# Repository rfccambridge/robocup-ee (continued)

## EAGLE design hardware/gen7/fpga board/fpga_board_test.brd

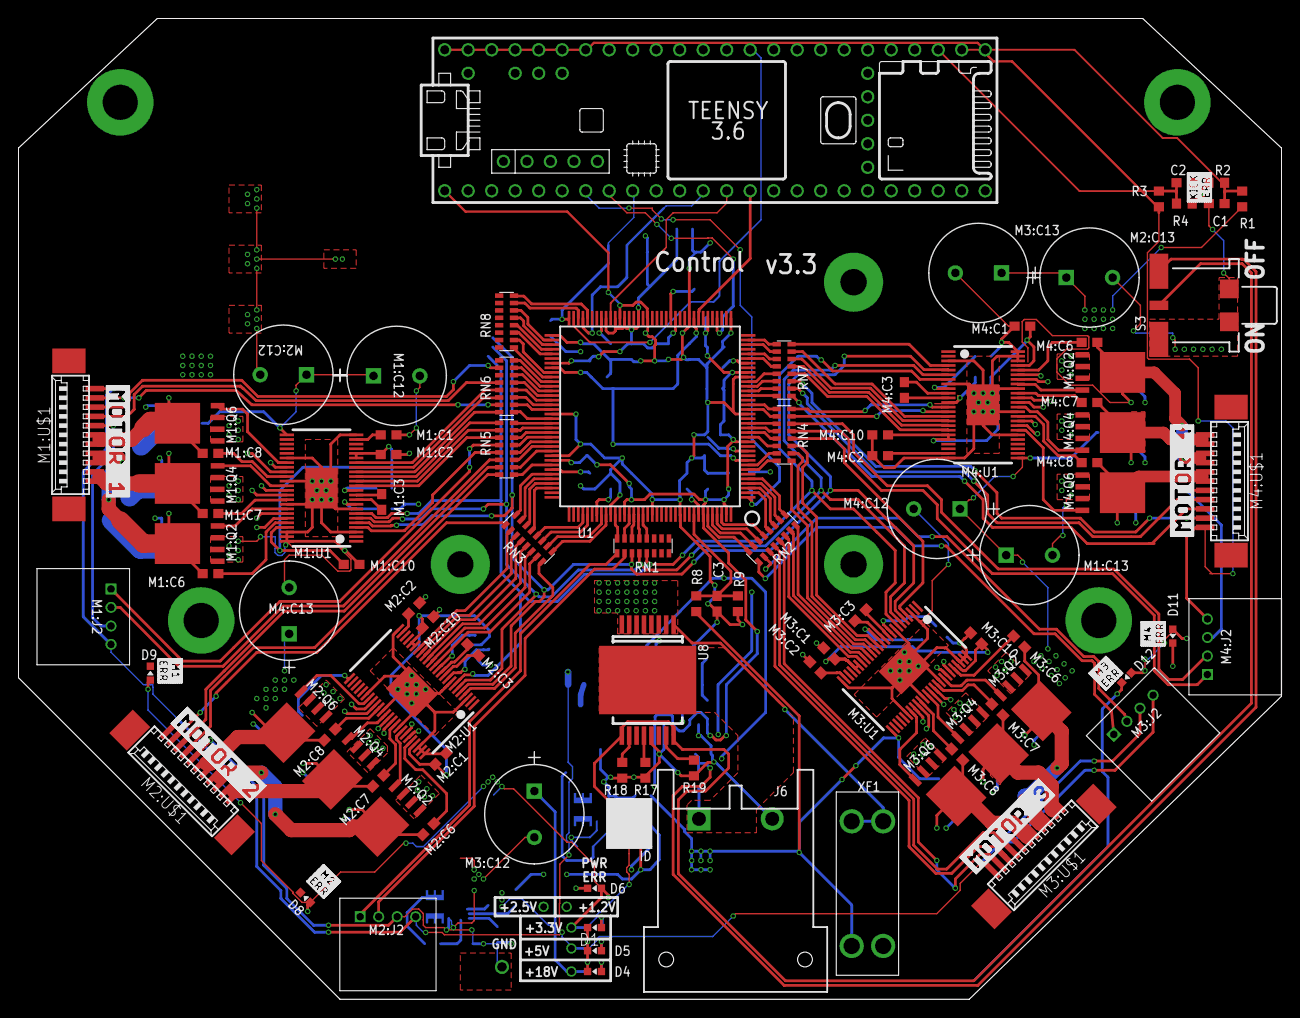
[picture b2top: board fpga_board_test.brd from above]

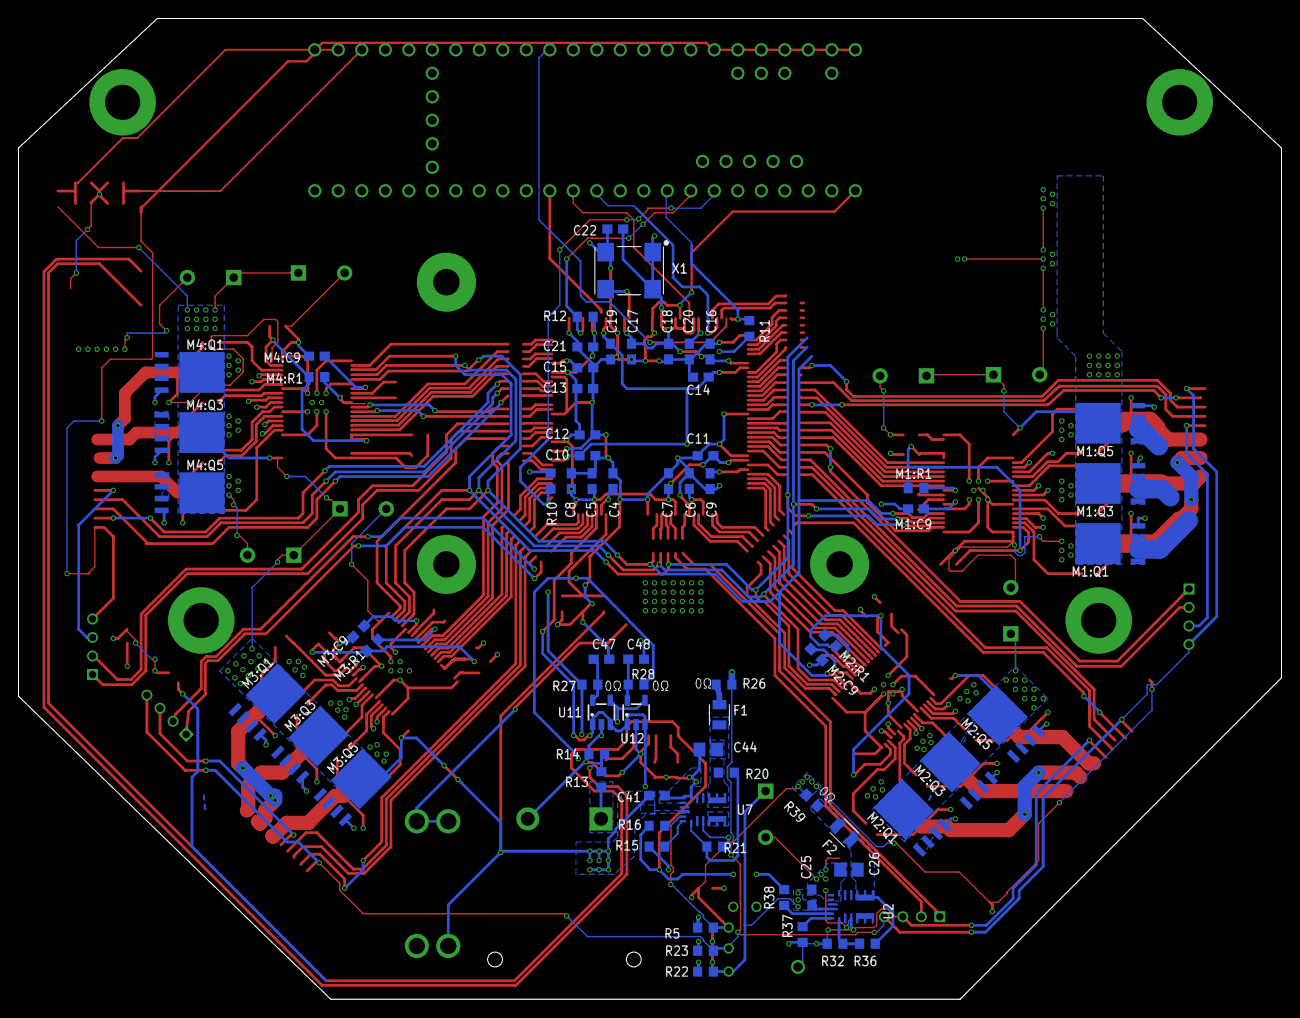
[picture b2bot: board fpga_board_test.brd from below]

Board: 6 copper layers, 136.5 x 106.0 mm, 175 parts (72 on the bottom side), 224 nets.

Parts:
C1: 0.1uF 50V; C0603
C2, C3, C4, C5, C6, C7, C8, C9, C10, C11, C12, C13, C14, C15, C16, C17, C18, C19, C20, C21, C22: 0.1uF; C0603
C25, C41: GRM188R6YA106MA73D; C0603
C26, C44: 22uF 16V; C0805
C47, C48: 1uF; C0603
D1, D4, D5: GREEN; CHIP-LED0603
D6, D8, D9, D11, D12: RED; CHIP-LED0603
F1, F2: 0805L200SLTHYR; FUSC2113X75
J6: DF22-2; DF22-2-H
M1:C1, M1:C2, M2:C1, M2:C2, M3:C1, M3:C2, M4:C1, M4:C2: 1uF; C0603
M1:C3, M2:C3, M3:C3, M4:C3: 0.022uF 50V; C0603
M1:C6, M1:C7, M1:C8, M1:C10, M2:C6, M2:C7, M2:C8, M2:C10, M3:C6, M3:C7, M3:C8, M3:C10, M4:C6, M4:C7, M4:C8, M4:C10: 0.1uF 50V; C0603
M1:C9, M2:C9, M3:C9, M4:C9: 2.2uF 50V; C0603
M1:C12, M1:C13, M2:C12, M2:C13, M3:C12, M3:C13, M4:C12, M4:C13: ECA-1HHG221; CAP_PAN_10X12.5
M1:J2, M2:J2, M3:J2, M4:J2: 4-PIN_2MM-H; 2MM-4-H
M1:Q1, M1:Q2, M1:Q3, M1:Q4, M1:Q5, M1:Q6, M2:Q1, M2:Q2, M2:Q3, M2:Q4, M2:Q5, M2:Q6, M3:Q1, M3:Q2, M3:Q3, M3:Q4, M3:Q5, M3:Q6, M4:Q1, M4:Q2, M4:Q3, M4:Q4, M4:Q5, M4:Q6: IRFH7545; PQFN_5X6_E
M1:R1, M2:R1, M3:R1, M4:R1: 10k; R0603
M1:U1, M2:U1, M3:U1, M4:U1: DRV8303DCA; TSSOP-48_PAD
M1:U$1, M2:U$1, M3:U$1, M4:U$1: MOTORCON; GEN3CON
R1: 68k 1%; R0603
R2, R3, R4: 10k 1%; R0603
R5, R18, R19, R22, R23: 1k; R0603
R8: 68k; R0603
R9, R17: 10k; R0603
R10, R12: 4.7k; R0603
R11: 330; R0603
R13: 270k; R0603
R14: 100k; R0603
R15: 43.2k; R0603
R16, R38: 150k; R0603
R20, R36: 160k 1%; R0603
R21: 30.1k 1%; R0603
R26, R27, R28, R39: 0; R0603
R32: 51.0k 1%; R0603
R37: 29.4k; R0603
RN1, RN2, RN3, RN4, RN5, RN6, RN7, RN8: 330; RA-8_2506
S3: 34EWMSP12M6RT
U1: XC3S250E-4TQG144C; TQFP144
U2, U7: MPM3620GQV-P
U8: VND5E006ASPTR-E; POWERSO-16
U11: MCP1824T-1202E/OT; SOT-23-5
U12: MCP1824T-2502E/OT; SOT-23-5
U$3: MOTOR-1
U$5: MOTOR-2
U$6: MOTOR-3
U$7: MOTOR-4
U$8: ERR-M1
U$10: TEENSY_3.5/3.6
U$12: ERR-M2
U$13: ERR-M3
U$14: ERR-M4
U$15: ERR-KICK
X1: ASV-18.432MHZ-EJ-T; ASV
XF1: 30A; 3557-2

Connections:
5V-LED: D5.A, R23.2
5V-LED1: D1.A, R5.2
18.5V-LED: D4.A, R22.1
!CS!-FPGA: U1.69, U$10.10/CS
+1.2V: C6.1, C10.1, C14.1, C19.1, R27.2, U1.9, U1.45, U1.80, U1.115
+1.2V-PRE: C47.1, R27.1, U11.5
+2.5V: C4.1, C9.1, C15.1, C20.1, R10.2, R11.2, R28.2, U1.30, U1.65, U1.102, U1.137
+2.5V-PRE: C48.1, R28.1, U12.5
+3.3V: C5.1, C7.1, C8.1, C11.1, C12.1, C13.1, C16.1, C17.1, C18.1, C21.1, C22.1, D6.A, D8.A, D9.A, D11.A, D12.A, R5.1, R12.1, R39.2, U1.13, U1.28, U1.42, U1.49, U1.57, U1.60, U1.62, U1.64, U1.79, U1.100, U1.121, U1.138, U1.143, U11.1, U11.3, U12.1, U12.3, X1.1, X1.4
+3.3V-FUSE: C26.1, F2.1, R36.2, U2.789
+5V: M1:J2.4, M1:U$1.1, M2:J2.4, M2:U$1.1, M3:J2.4, M3:U$1.1, M4:J2.4, M4:U$1.1, R3.1, R23.1, R26.2, U$10.VIN
+5V-FUSE: C44.1, F1.1, R20.2, U7.789
+18.5V: C25.1, C41.1, M1:C12.1, M1:C13.1, M1:Q1.5678, M1:Q3.5678, M1:Q5.5678, M1:U1.25, M2:C12.1, M2:C13.1, M2:Q1.5678, M2:Q3.5678, M2:Q5.5678, M2:U1.25, M3:C12.1, M3:C13.1, M3:Q1.5678, M3:Q3.5678, M3:Q5.5678, M3:U1.25, M4:C12.1, M4:C13.1, M4:Q1.5678, M4:Q3.5678, M4:Q5.5678, M4:U1.25, R1.1, R8.1, R22.2, U2.16, U7.16, XF1.3, XF1.4
AAM: R15.2, U7.18
AAM1: R37.2, U2.18
BATT-FPGA: C3.1, R8.2, R9.1, U1.136
CS1: R18.2, U8.10
CS2: R19.2, U8.15
CS-DIS: R17.2, U8.12
EN: R16.2, U7.17
EN1: R38.2, U2.17
EN-PWR: R16.1, R38.1, S3.2, U8.9, U8.16
EN-PWR-PRE: R13.1, R14.2, S3.1
FB: R20.1, R21.2, U7.1
FB1: R32.2, R36.1, U2.1
FPGA-CLK: U1.50, X1.3
FPGA-DONE: R11.1, U1.72, U$10.7
FPGA-INIT: R12.2, U1.40, U$10.6
FPGA-PROG: R10.1, U1.1, U$10.5
GND: C1.2, C2.2, C3.2, C4.2, C5.2, C6.2, C7.2, C8.2, C9.2, C10.2, C11.2, C12.2, C13.2, C14.2, C15.2, C16.2, C17.2, C18.2, C19.2, C20.2, C21.2, C22.2, C25.2, C26.2, C41.2, C44.2, C47.2, C48.2, D1.C, D4.C, D5.C, J6.2, M1:C1.2, M1:C2.2, M1:C9.2, M1:C10.2, M1:C12.2, M1:C13.2, M1:J2.3, M1:Q2.1, M1:Q2.2, M1:Q2.3, M1:Q4.1, M1:Q4.2, M1:Q4.3, M1:Q6.1, M1:Q6.2, M1:Q6.3, M1:U1.3, M1:U1.8, M1:U1.24, M1:U1.30, M1:U1.35, M1:U1.40, M1:U1.46, M1:U1.47, M1:U1.48, M1:U1.PAD, M1:U$1.5, M2:C1.2, M2:C2.2, M2:C9.2, M2:C10.2, M2:C12.2, M2:C13.2, M2:J2.3, M2:Q2.1, M2:Q2.2, M2:Q2.3, M2:Q4.1, M2:Q4.2, M2:Q4.3, M2:Q6.1, M2:Q6.2, M2:Q6.3, M2:U1.3, M2:U1.8, M2:U1.24, M2:U1.30, M2:U1.35, M2:U1.40, M2:U1.46, M2:U1.47, M2:U1.48, M2:U1.PAD, M2:U$1.5, M3:C1.2, M3:C2.2, M3:C9.2, M3:C10.2, M3:C12.2, M3:C13.2, M3:J2.3, M3:Q2.1, M3:Q2.2, M3:Q2.3, M3:Q4.1, M3:Q4.2, M3:Q4.3, M3:Q6.1, M3:Q6.2, M3:Q6.3, M3:U1.3, M3:U1.8, M3:U1.24, M3:U1.30, M3:U1.35, M3:U1.40, M3:U1.46, M3:U1.47, M3:U1.48, M3:U1.PAD, M3:U$1.5, M4:C1.2, M4:C2.2, M4:C9.2, M4:C10.2, M4:C12.2, M4:C13.2, M4:J2.3, M4:Q2.1, M4:Q2.2, M4:Q2.3, M4:Q4.1, M4:Q4.2, M4:Q4.3, M4:Q6.1, M4:Q6.2, M4:Q6.3, M4:U1.3, M4:U1.8, M4:U1.24, M4:U1.30, M4:U1.35, M4:U1.40, M4:U1.46, M4:U1.47, M4:U1.48, M4:U1.PAD, M4:U$1.5, R2.2, R4.2, R9.2, R14.1, R15.1, R17.1, R18.1, R19.1, R21.1, R32.1, R37.1, S3.3, S3.LEG1, S3.LEG3, U1.11, U1.19, U1.27, U1.37, U1.46, U1.55, U1.61, U1.73, U1.90, U1.99, U1.118, U1.127, U1.133, U2.3, U2.12, U2.13, U2.14, U7.3, U7.12, U7.13, U7.14, U8.13, U11.2, U12.2, U$10.GND, X1.2
M1-!CS: M1:U1.4, RN5.13
M1-A-H: M1:U1.15, RN5.9
M1-A-L: M1:U1.16, RN6.16
M1-B-H: M1:U1.13, RN5.11
M1-B-L: M1:U1.14, RN5.10
M1-C-H: M1:U1.17, RN6.14
M1-C-L: M1:U1.18, RN6.13
M1-ENC-A: M1:J2.2, RN5.14
M1-ENC-B: M1:J2.1, RN5.12
M1-H1: M1:U$1.3, RN6.10
M1-H2: M1:U$1.4, RN6.12
M1-H3: M1:U$1.2, RN6.15
M1:+3.3V: M1:C1.1, M1:C10.1, M1:R1.1, M1:U1.19, M1:U1.20, M1:U1.45
M1:AVDD: M1:C2.1, M1:U1.23
M1:BST-A: M1:C6.1, M1:U1.44
M1:BST-B: M1:C7.1, M1:U1.39
M1:BST-C: M1:C8.1, M1:U1.34
M1:CP1: M1:C3.1, M1:U1.10
M1:CP2: M1:C3.2, M1:U1.11
M1:EN-GATE: M1:R1.2, M1:U1.12
M1:GH-A: M1:Q1.4, M1:U1.43
M1:GH-B: M1:Q3.4, M1:U1.38
M1:GH-C: M1:Q5.4, M1:U1.33
M1:GL-A: M1:Q2.4, M1:U1.41
M1:GL-B: M1:Q4.4, M1:U1.36
M1:GL-C: M1:Q6.4, M1:U1.31
M1:GVDD: M1:C9.1, M1:U1.9
M1:PHASE-A: M1:C7.2, M1:Q3.1, M1:Q3.2, M1:Q3.3, M1:Q4.5678, M1:U1.37, M1:U$1.10, M1:U$1.11
M1:PHASE-B: M1:C6.2, M1:Q1.1, M1:Q1.2, M1:Q1.3, M1:Q2.5678, M1:U1.42, M1:U$1.8, M1:U$1.9
M1:PHASE-C: M1:C8.2, M1:Q5.1, M1:Q5.2, M1:Q5.3, M1:Q6.5678, M1:U1.32, M1:U$1.6, M1:U$1.7
M2-!CS: M2:U1.4, RN3.16
M2-A-H: M2:U1.15, RN3.13
M2-A-L: M2:U1.16, RN3.12
M2-B-H: M2:U1.13, RN3.15
M2-B-L: M2:U1.14, RN3.14
M2-C-H: M2:U1.17, RN3.11
M2-C-L: M2:U1.18, RN3.10
M2-ENC-A: M2:J2.2, RN1.10
M2-ENC-B: M2:J2.1, RN1.9
M2-H1: M2:U$1.3, RN5.15
M2-H2: M2:U$1.4, RN5.16
M2-H3: M2:U$1.2, RN3.9
M2:+3.3V: M2:C1.1, M2:C10.1, M2:R1.1, M2:U1.19, M2:U1.20, M2:U1.45
M2:AVDD: M2:C2.1, M2:U1.23
M2:BST-A: M2:C6.1, M2:U1.44
M2:BST-B: M2:C7.1, M2:U1.39
M2:BST-C: M2:C8.1, M2:U1.34
M2:CP1: M2:C3.1, M2:U1.10
M2:CP2: M2:C3.2, M2:U1.11
M2:EN-GATE: M2:R1.2, M2:U1.12
M2:GH-A: M2:Q1.4, M2:U1.43
M2:GH-B: M2:Q3.4, M2:U1.38
M2:GH-C: M2:Q5.4, M2:U1.33
M2:GL-A: M2:Q2.4, M2:U1.41
M2:GL-B: M2:Q4.4, M2:U1.36
M2:GL-C: M2:Q6.4, M2:U1.31
M2:GVDD: M2:C9.1, M2:U1.9
M2:PHASE-A: M2:C7.2, M2:Q3.1, M2:Q3.2, M2:Q3.3, M2:Q4.5678, M2:U1.37, M2:U$1.10, M2:U$1.11
M2:PHASE-B: M2:C6.2, M2:Q1.1, M2:Q1.2, M2:Q1.3, M2:Q2.5678, M2:U1.42, M2:U$1.8, M2:U$1.9
M2:PHASE-C: M2:C8.2, M2:Q5.1, M2:Q5.2, M2:Q5.3, M2:Q6.5678, M2:U1.32, M2:U$1.6, M2:U$1.7
M3-!CS: M3:U1.4, RN4.12
M3-A-H: M3:U1.15, RN4.9
M3-A-L: M3:U1.16, RN2.16
M3-B-H: M3:U1.13, RN4.11
M3-B-L: M3:U1.14, RN4.10
M3-C-H: M3:U1.17, RN2.15
M3-C-L: M3:U1.18, RN2.14
M3-ENC-A: M3:J2.2, RN2.10
M3-ENC-B: M3:J2.1, RN2.9
M3-H1: M3:U$1.3, RN2.11
M3-H2: M3:U$1.4, RN2.12
M3-H3: M3:U$1.2, RN2.13
M3:+3.3V: M3:C1.1, M3:C10.1, M3:R1.1, M3:U1.19, M3:U1.20, M3:U1.45
M3:AVDD: M3:C2.1, M3:U1.23
M3:BST-A: M3:C6.1, M3:U1.44
M3:BST-B: M3:C7.1, M3:U1.39
M3:BST-C: M3:C8.1, M3:U1.34
M3:CP1: M3:C3.1, M3:U1.10
M3:CP2: M3:C3.2, M3:U1.11
M3:EN-GATE: M3:R1.2, M3:U1.12
M3:GH-A: M3:Q1.4, M3:U1.43
M3:GH-B: M3:Q3.4, M3:U1.38
M3:GH-C: M3:Q5.4, M3:U1.33
M3:GL-A: M3:Q2.4, M3:U1.41
M3:GL-B: M3:Q4.4, M3:U1.36
M3:GL-C: M3:Q6.4, M3:U1.31
M3:GVDD: M3:C9.1, M3:U1.9
M3:PHASE-A: M3:C7.2, M3:Q3.1, M3:Q3.2, M3:Q3.3, M3:Q4.5678, M3:U1.37, M3:U$1.10, M3:U$1.11
M3:PHASE-B: M3:C6.2, M3:Q1.1, M3:Q1.2, M3:Q1.3, M3:Q2.5678, M3:U1.42, M3:U$1.8, M3:U$1.9
M3:PHASE-C: M3:C8.2, M3:Q5.1, M3:Q5.2, M3:Q5.3, M3:Q6.5678, M3:U1.32, M3:U$1.6, M3:U$1.7
M4-!CS: M4:U1.4, RN7.16
M4-A-H: M4:U1.15, RN7.15
M4-A-L: M4:U1.16, RN7.14
M4-B-H: M4:U1.13, RN4.16
M4-B-L: M4:U1.14, RN4.15
M4-C-H: M4:U1.17, RN7.13
M4-C-L: M4:U1.18, RN7.12
M4-ENC-A: M4:J2.2, RN4.14
M4-ENC-B: M4:J2.1, RN4.13
M4-H1: M4:U$1.3, RN7.9
M4-H2: M4:U$1.4, RN7.10
M4-H3: M4:U$1.2, RN7.11
M4:+3.3V: M4:C1.1, M4:C10.1, M4:R1.1, M4:U1.19, M4:U1.20, M4:U1.45
M4:AVDD: M4:C2.1, M4:U1.23
M4:BST-A: M4:C6.1, M4:U1.44
M4:BST-B: M4:C7.1, M4:U1.39
M4:BST-C: M4:C8.1, M4:U1.34
M4:CP1: M4:C3.1, M4:U1.10
M4:CP2: M4:C3.2, M4:U1.11
M4:EN-GATE: M4:R1.2, M4:U1.12
M4:GH-A: M4:Q1.4, M4:U1.43
M4:GH-B: M4:Q3.4, M4:U1.38
M4:GH-C: M4:Q5.4, M4:U1.33
M4:GL-A: M4:Q2.4, M4:U1.41
M4:GL-B: M4:Q4.4, M4:U1.36
M4:GL-C: M4:Q6.4, M4:U1.31
M4:GVDD: M4:C9.1, M4:U1.9
M4:PHASE-A: M4:C7.2, M4:Q3.1, M4:Q3.2, M4:Q3.3, M4:Q4.5678, M4:U1.37, M4:U$1.10, M4:U$1.11
M4:PHASE-B: M4:C6.2, M4:Q1.1, M4:Q1.2, M4:Q1.3, M4:Q2.5678, M4:U1.42, M4:U$1.8, M4:U$1.9
M4:PHASE-C: M4:C8.2, M4:Q5.1, M4:Q5.2, M4:Q5.3, M4:Q6.5678, M4:U1.32, M4:U$1.6, M4:U$1.7
MISO-AUX: M1:U1.6, M2:U1.6, M3:U1.6, M4:U1.6, RN1.12
MISO-FPGA: U1.44, U$10.12/MISO
MOSI-AUX: M1:U1.5, M2:U1.5, M3:U1.5, M4:U1.5, RN1.11
MOSI-FPGA: U1.63, U$10.11/MOSI
unnamed: F2.2, R39.1
unnamed: F1.2, R26.1
PWR-ERR: D6.C, U11.4, U12.4
R-P1: RN8.1, U1.82
R-P2: RN8.2, U1.81
R-P3: RN8.3, U1.77
R-P4: RN8.4, U1.76
R-P5: RN8.5, U1.75
R-P6: RN8.6, U1.74
R-P7: RN8.7, U1.70
R-P8: RN8.8, U1.68
R-P9: RN6.1, U1.91
R-P10: RN6.2, U1.89
R-P11: RN6.3, U1.88
R-P12: RN6.4, U1.87
R-P13: RN6.5, U1.86
R-P14: RN6.6, U1.85
R-P15: RN6.7, U1.84
R-P16: RN6.8, U1.83
R-P17: RN5.1, U1.101
R-P18: RN5.2, U1.98
R-P19: RN5.3, U1.97
R-P20: RN5.4, U1.96
R-P21: RN5.5, U1.95
R-P22: RN5.6, U1.94
R-P23: RN5.7, U1.93
R-P24: RN5.8, U1.92
R-P25: RN3.1, U1.117
R-P26: RN3.2, U1.116
R-P27: RN3.3, U1.113
R-P28: RN3.4, U1.112
R-P29: RN3.5, U1.106
R-P30: RN3.6, U1.105
R-P31: RN3.7, U1.104
R-P32: RN3.8, U1.103
R-P36: RN1.4, U1.125
R-P37: RN1.5, U1.124
R-P38: RN1.6, U1.123
R-P39: RN1.7, U1.122
R-P40: RN1.8, U1.119
R-P41: RN2.1, U1.5
R-P42: RN2.2, U1.4
R-P43: RN2.3, U1.3
R-P44: RN2.4, U1.2
R-P45: RN2.5, U1.142
R-P46: RN2.6, U1.141
R-P47: RN2.7, U1.140
R-P48: RN2.8, U1.139
R-P49: RN4.1, U1.21
R-P50: RN4.2, U1.20
R-P51: RN4.3, U1.17
R-P52: RN4.4, U1.16
R-P53: RN4.5, U1.15
R-P54: RN4.6, U1.14
R-P55: RN4.7, U1.8
R-P56: RN4.8, U1.7
R-P57: RN7.1, U1.35
R-P58: RN7.2, U1.34
R-P59: RN7.3, U1.32
R-P60: RN7.4, U1.31
R-P61: RN7.5, U1.26
R-P62: RN7.6, U1.25
R-P63: RN7.7, U1.24
R-P64: RN7.8, U1.23
SCK-AUX: M1:U1.7, M2:U1.7, M3:U1.7, M4:U1.7, RN1.13
SCK-FPGA: U1.71, U$10.13/SCK
SENSE-BATT: C1.1, R1.2, R2.1, U$10.34/A15
SENSE-VIN: C2.1, R3.2, R4.1, U$10.35/A16
VBATT: U8.1, U8.2, U8.3, U8.4, U8.5, U8.6, U8.7, U8.8, XF1.1, XF1.2
VIN: J6.1, R13.2, U8.17

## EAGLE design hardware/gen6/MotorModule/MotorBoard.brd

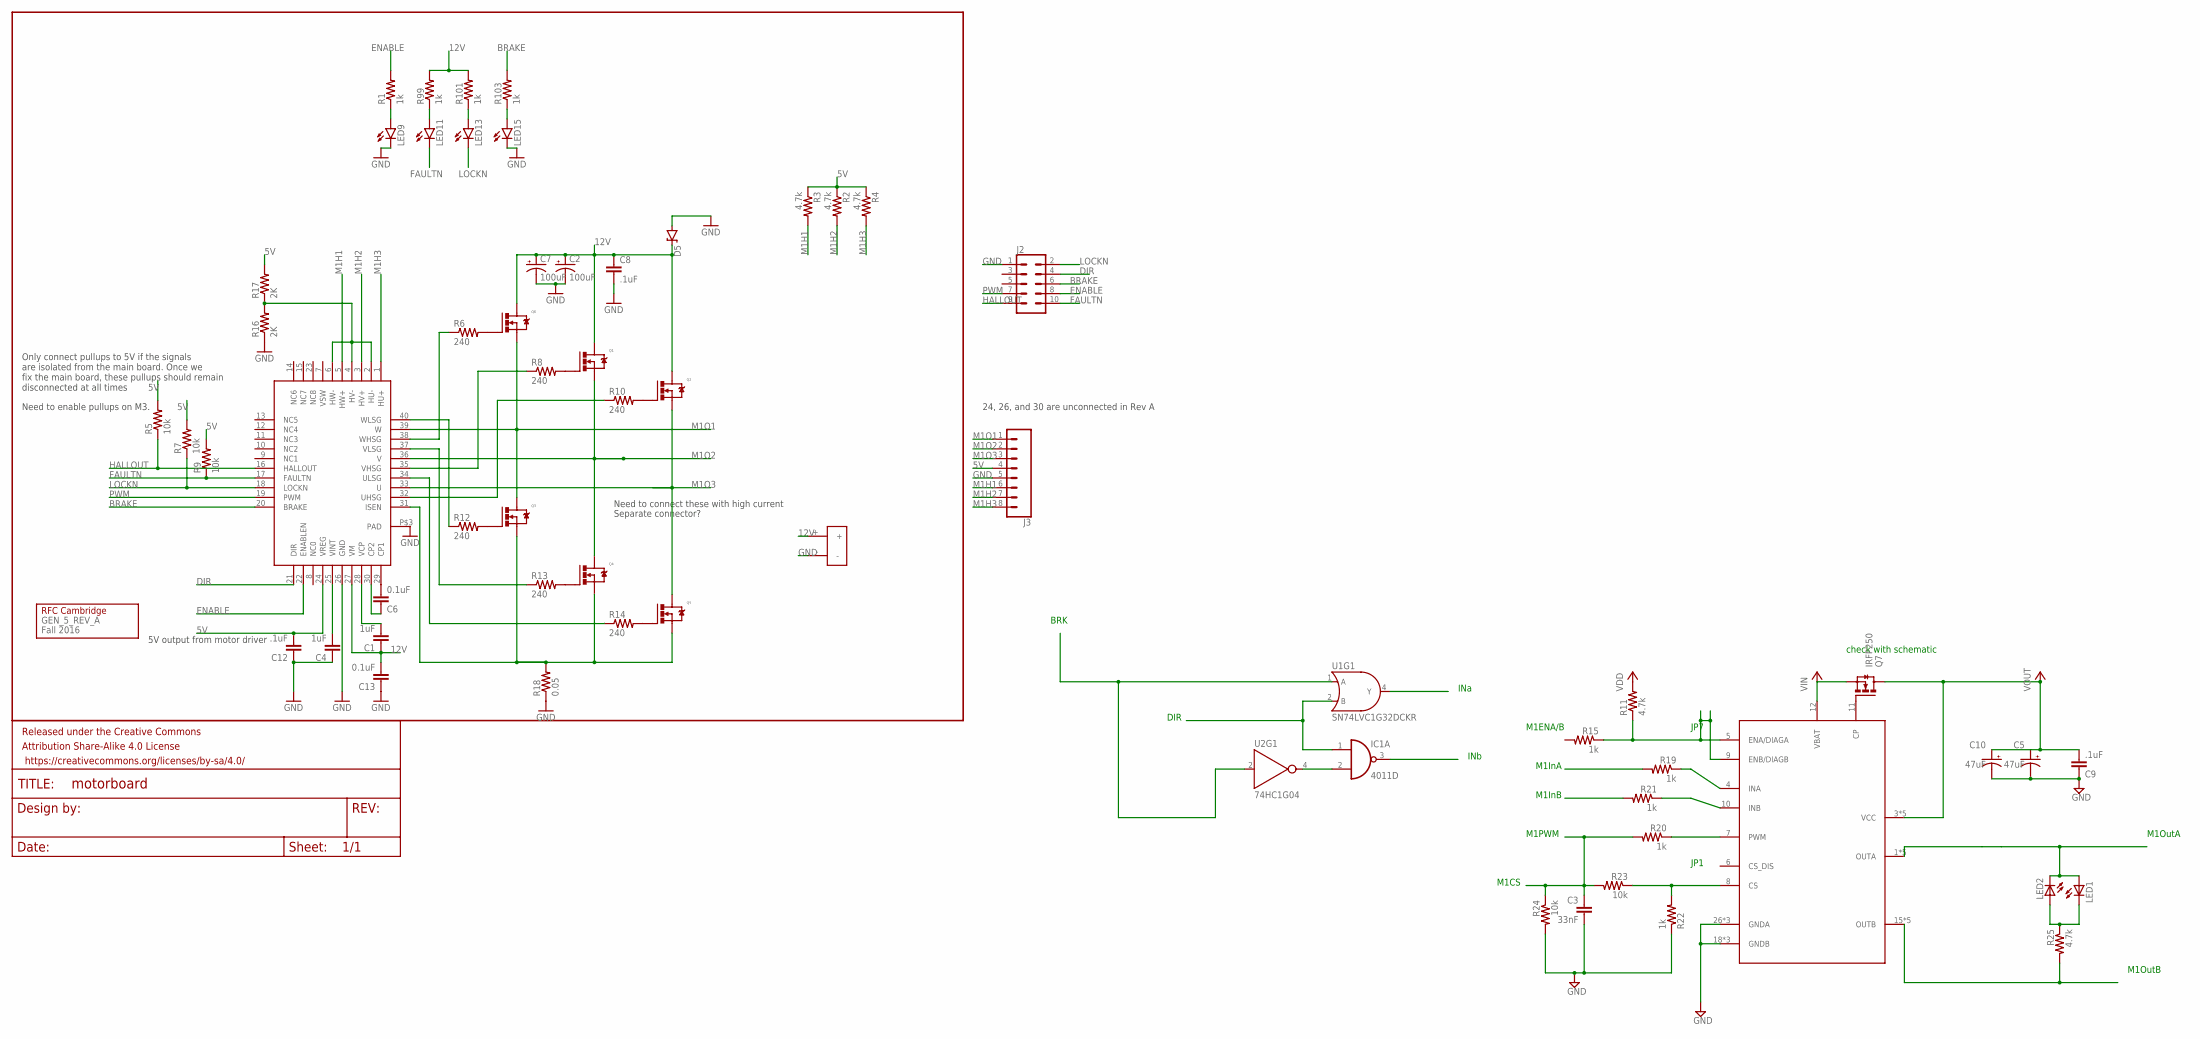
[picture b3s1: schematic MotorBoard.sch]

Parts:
C1, C4: 1uF; 0805
C2, C7: 100uF; PANASONIC_D
C3: 33nF; 0805
C5, C10: 47uF; 085CS_1AW
C6, C13: 0.1uF; 0805
C8, C9, C12: .1uF; 0805
D5: DIODE-ZENERDO214AC; DO214AC
FRAME7: FRAME-LETTER; CREATIVE_COMMONS
GEN_5_REV_A: Fall 2016; LOGO
IC1: 4011D; SO14
J2: CONN_05X2SHD; 2X5-SHROUDED
J3: CONN_08LONGPADS; 1X08_LONGPADS
LED1, LED2: LED; SMARTLED-TTW
LED9, LED11, LED13, LED15: LED1206; LED-1206
Q1, Q2, Q3, Q4, Q5, Q6: N-MOSFET; DPAK
Q7: IRFP250; TO-247AD-V
R1, R15, R19, R20, R21, R22, R99, R101, R103: 1k; 0805
R2, R3, R4, R11, R25: 4.7k; 0805
R5, R7, R9, R23, R24: 10k; 0805
R6, R8, R10, R12, R13, R14: 240; 0805
R16, R17: 2K; 0805
R18: 0.05; R2512
U1: SN74LVC1G32DCKR; SOT23-5
U2: 74HC1G04; SOT353
U$1: DRV8307; QFN40-6X6
U$2: POWER_CONN_2X1
U$3: VNH5019A-E; MULTIPOWERSO-30

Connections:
5V: C12.2, J3.4, R2.1, R3.1, R4.1, R5.2, R7.2, R9.2, R17.2, U$1.24 (VREG)
12V: C1.1, C2.+, C7.+, C8.1, C13.2, D5.C, Q1.DRAIN, Q2.DRAIN, Q6.DRAIN, R99.2, R101.2, U$1.27 (VM), U$2.+
+5V: Q7.S, R11.2, U$3.12 (VBAT)
BRAKE: J2.6, R103.2, U$1.20 (BRAKE)
DIR: J2.4, U$1.21 (DIR)
ENABLE: J2.8, R1.2, U$1.22 (ENABLEN)
FAULTN: J2.10, LED11.C, R9.1, U$1.17 (FAULTN)
GND: C2.-, C3.2, C4.1, C5.-, C7.-, C8.2, C9.1, C10.-, C12.1, C13.1, D5.A, J2.1, J3.5, LED9.C, LED15.C, R16.1, R18.1, R22.1, R24.2, U$1.26 (GND), U$1.P$3 (PAD), U$2.-, U$3.18 (GNDB), U$3.26 (GNDA)
HALLOUT: J2.9, R5.1, U$1.16 (HALLOUT)
LOCKN: J2.2, LED13.C, R7.1, U$1.18 (LOCKN)
M1H1: J3.6, R3.2, U$1.5 (HW+)
M1H2: J3.7, R2.2, U$1.3 (HV+)
M1H3: J3.8, R4.2, U$1.1 (HU+)
M1O1: J3.1, Q3.DRAIN, Q6.SOURCE, U$1.39 (W)
M1O2: J3.2, Q1.SOURCE, Q4.DRAIN, U$1.36 (V)
M1O3: J3.3, Q2.SOURCE, Q5.DRAIN, U$1.33 (U)
unnamed: LED9.A, R1.1
unnamed: C6.2, U$1.29 (CP1)
unnamed: C1.2, U$1.28 (VCP)
unnamed: Q6.GATE, R6.2
unnamed: Q1.GATE, R8.2
unnamed: C6.1, U$1.30 (CP2)
unnamed: Q2.GATE, R10.2
unnamed: Q3.GATE, R12.2
unnamed: R11.1, R15.1, U$3.5 (ENA/DIAGA), U$3.9 (ENB/DIAGB)
unnamed: Q4.GATE, R13.2
unnamed: Q5.GATE, R14.2
unnamed: C4.2, U$1.25 (VINT)
unnamed: R6.1, U$1.38 (WHSG)
unnamed: R14.1, U$1.34 (ULSG)
unnamed: R13.1, U$1.37 (VLSG)
unnamed: R12.1, U$1.40 (WLSG)
unnamed: R8.1, U$1.35 (VHSG)
unnamed: R10.1, U$1.32 (UHSG)
unnamed: R16.2, R17.1, U$1.2 (HU-), U$1.4 (HV-), U$1.6 (HW-)
unnamed: R19.1, U$3.4 (INA)
unnamed: U1.1 (A), U2.2 (A)
unnamed: IC1.2 (I1), U2.4 (Y)
unnamed: IC1.1 (I0), U1.2 (B)
unnamed: R21.1, U$3.10 (INB)
unnamed: R20.1, U$3.7 (PWM)
unnamed: R22.2, R23.1, U$3.8 (CS)
unnamed: C3.1, R20.2, R23.2, R24.1
unnamed: C5.+, C9.2, C10.+, Q7.D, U$3.3 (VCC)
unnamed: R25.2, U$3.15 (OUTB)
unnamed: LED1.C@1 (C), LED2.A@1 (A), R25.1
unnamed: LED1.A@1 (A), LED2.C@1 (C), U$3.1 (OUTA)
unnamed: LED11.A, R99.1
unnamed: LED13.A, R101.1
unnamed: LED15.A, R103.1
unnamed: Q7.G, U$3.11 (CP)
O1: Q3.SOURCE, Q4.SOURCE, Q5.SOURCE, R18.2, U$1.31 (ISEN)
PWM: J2.7, U$1.19 (PWM)
VDD: IC1.14 (VDD)
VSS: IC1.7 (VSS)

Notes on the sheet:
5V output from motor driver
Need to connect these with high current
Separate connector?
24, 26, and 30 are unconnected in Rev A
Need to enable pullups on M3.
Only connect pullups to 5V if the signals are isolated from the main board. Once we fix the main board, these pullups should remain disconnected at all times
BRK
DIR
INa
INb
check with schematic
JP7
JP1
M1ENA/B
M1InA
M1InB
M1CS
M1OutB
M1OutA
M1PWM

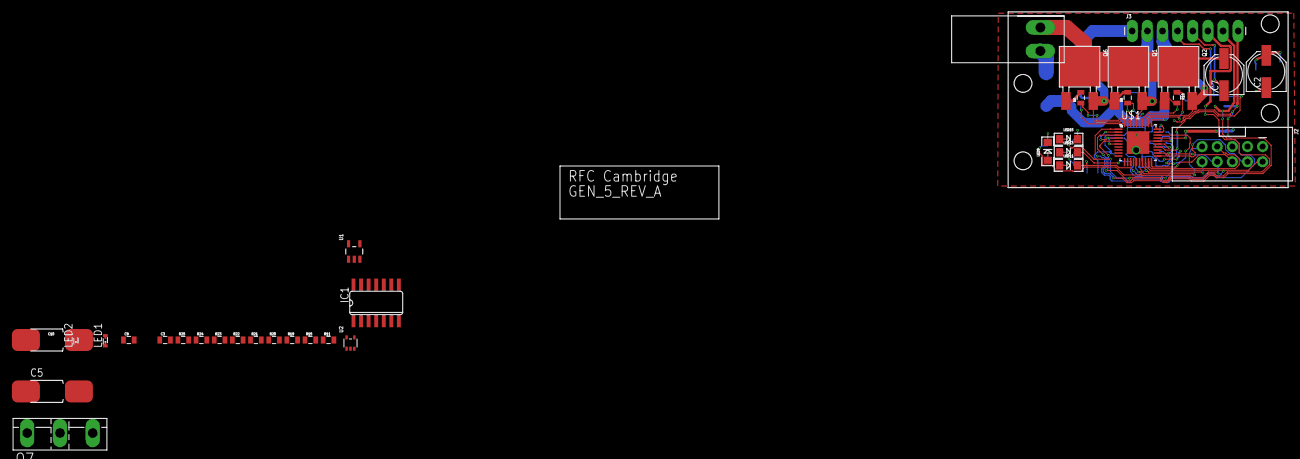
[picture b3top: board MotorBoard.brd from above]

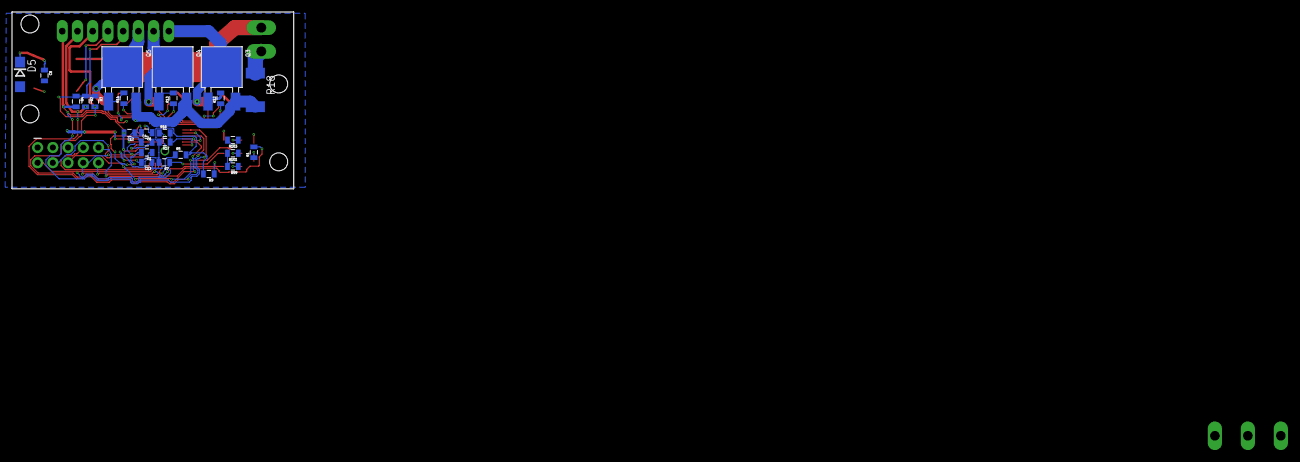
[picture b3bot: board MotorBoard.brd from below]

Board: 2 copper layers, 47.0 x 29.5 mm, 63 parts (26 on the bottom side), 47 nets.

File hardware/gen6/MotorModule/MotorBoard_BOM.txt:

Partlist exported from C:/Users/joncr_000/robocup/robocup-ee/hardware/gen5/MotorModule/MotorBoard.sch at 12/26/2016 16:16:32

Part        Value              Device             Package          Description               MF MPN             OC_FARNELL OC_NEWARK PROD_ID   
C1          1uF                CAP0805            0805             Capacitor                                                                   
C2          100uF              CAP-POLAR          PANASONIC_D      Cap Alum Polarized                                                CAP-10547 
C3          .1uF               CAP0805            0805             Capacitor                                                                   
C4          1uF                CAP0805            0805             Capacitor                                                                   
C5          .1uF               CAP0805            0805             Capacitor                                                                   
C6          0.1uF              CAP0805            0805             Capacitor                                                                   
C7          100uF              CAP-POLAR          PANASONIC_D      Cap Alum Polarized                                                CAP-10547 
C8          .1uF               CAP0805            0805             Capacitor                                                                   
C12         .1uF               CAP0805            0805             Capacitor                                                                   
C13         0.1uF              CAP0805            0805             Capacitor                                                                   
D5          DIODE-ZENERDO214AC DIODE-ZENERDO214AC DO214AC          Zener Diode                                                                 
FRAME7      FRAME-LETTER       FRAME-LETTER       CREATIVE_COMMONS Schematic Frame                                                             
GEN_5_REV_A Fall 2016          LOGO               LOGO                                                                                         
IC2         3.3V REG           LT1129CST5         SOT223           VOLTAGE REGULATOR            LT1129CST-5#PBF 1663375    57M2069             
J1          M20X2SHROUDED      M20X2SHROUDED      2X20_SHROUDED    0.1" spaced headers                                               CONN-12263
LED9                           LED1206            LED-1206         LEDs                                                                        
LED11                          LED1206            LED-1206         LEDs                                                                        
LED13                          LED1206            LED-1206         LEDs                                                                        
LED15                          LED1206            LED-1206         LEDs                                                                        
Q1                             N-MOSFET           DPAK             N-Channel Power Mosfet                                                      
Q2                             N-MOSFET           DPAK             N-Channel Power Mosfet                                                      
Q3                             N-MOSFET           DPAK             N-Channel Power Mosfet                                                      
Q4                             N-MOSFET           DPAK             N-Channel Power Mosfet                                                      
Q5                             N-MOSFET           DPAK             N-Channel Power Mosfet                                                      
Q6                             N-MOSFET           DPAK             N-Channel Power Mosfet                                                      
R1          1k                 RESISTOR0805-RES   0805             Resistor                                                                    
R2          4.7k               RESISTOR0805-RES   0805             Resistor                                                                    
R3          4.7k               RESISTOR0805-RES   0805             Resistor                                                                    
R4          4.7k               RESISTOR0805-RES   0805             Resistor                                                                    
R6          240                RESISTOR0805-RES   0805             Resistor                                                                    
R7          1k                 RESISTOR0805-RES   0805             Resistor                                                                    
R8          240                RESISTOR0805-RES   0805             Resistor                                                                    
R9          1k                 RESISTOR0805-RES   0805             Resistor                                                                    
R10         240                RESISTOR0805-RES   0805             Resistor                                                                    
R12         240                RESISTOR0805-RES   0805             Resistor                                                                    
R13         240                RESISTOR0805-RES   0805             Resistor                                                                    
R14         240                RESISTOR0805-RES   0805             Resistor                                                                    
R16         2K                 RESISTOR0805-RES   0805             Resistor                                                                    
R17         2K                 RESISTOR0805-RES   0805             Resistor                                                                    
R18         0.05               R-US_R2512         R2512            RESISTOR, American symbol                                                   
R63         1k                 RESISTOR0805-RES   0805             Resistor                                                                    
R99         1k                 RESISTOR0805-RES   0805             Resistor                                                                    
R101        1k                 RESISTOR0805-RES   0805             Resistor                                                                    
R103        1k                 RESISTOR0805-RES   0805             Resistor                                                                    
U$1         DRV8307            DRV8307            QFN40-6X6                                                                                    
U$2         INDUCTOR           INDUCTOR           0805

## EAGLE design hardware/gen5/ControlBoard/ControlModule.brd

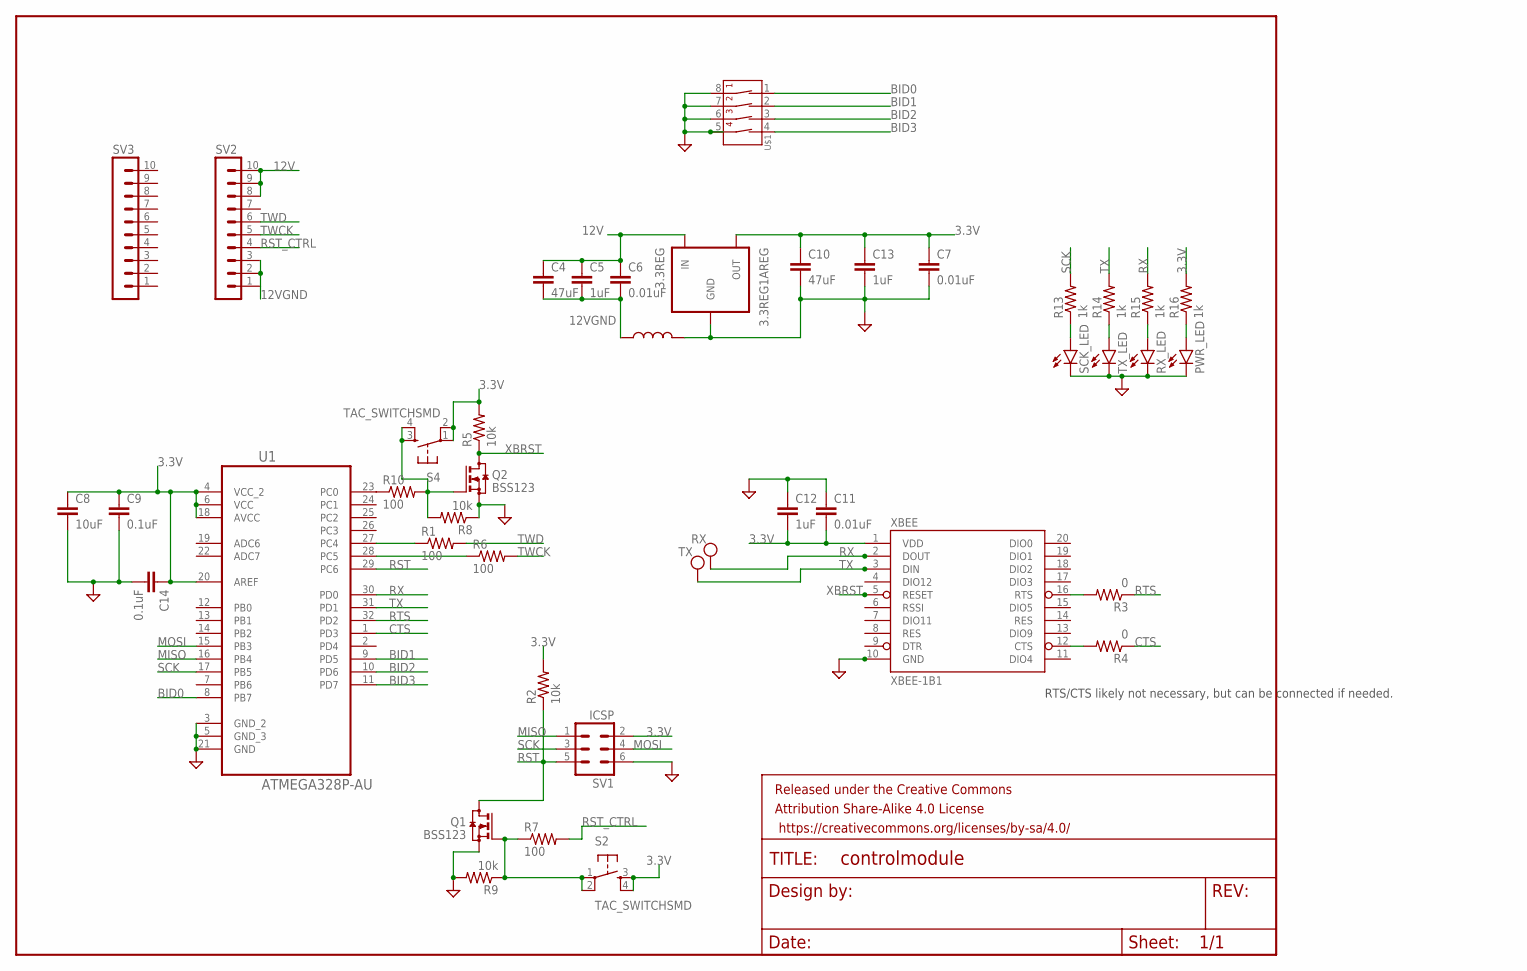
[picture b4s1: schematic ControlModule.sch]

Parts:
3.3REG: 3.3REG1AREG; DPAK
C4, C10: 47uF; 1206
C5, C12, C13: 1uF; 0805
C6, C7, C11: 0.01uF; 0805
C8: 10uF; 0805
C9, C14: 0.1uF; 0805
FRAME1: FRAME-LETTER; CREATIVE_COMMONS
PWR_LED: LED1206; LED-1206
Q1, Q2: BSS123; SOT23
R1, R6, R7, R10: 100; 0805
R2, R5, R8, R9: 10k; 0805
R3, R4: 0; 0805
R13, R14, R15, R16: 1k; 0805
RX: TEST_PT; TESTING_PT
RX_LED: LED1206; LED-1206
S2, S4: TAC_SWITCHSMD; TACTILE-SWITCH-SMD
SCK_LED: LED1206; LED-1206
SV1: ICSP; MA03-2
SV2, SV3: MA10-1W
TX: TEST_PT; TESTING_PT
TX_LED: LED1206; LED-1206
U1: ATMEGA328P-AU; QFP80P900X900X120-32N
U$1: 4-POS-DIP; 4-POS-DIP-SMD
U$2: INDUCTOR; 0805
XBEE: XBEE-1B1; XBEE-1

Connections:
3.3V: 3.3REG.SOURCE (OUT), C7.1, C8.1, C9.1, C10.1, C11.2, C12.2, C13.1, C14.1, R2.2, R5.2, R16.2, S2.3, S2.4, S4.1, S4.2, SV1.2, U1.4 (VCC_2), U1.6 (VCC), U1.18 (AVCC), U1.20 (AREF), XBEE.1 (VDD)
12V: 3.3REG.GATE (IN), C4.1, C5.1, C6.1, SV2.8, SV2.9, SV2.10
12VGND: C4.2, C5.2, C6.2, SV2.1, SV2.2, SV2.3, U$2.1
BID0: U1.8 (PB7), U$1.1 (1A)
BID1: U1.9 (PD5), U$1.2 (2A)
BID2: U1.10 (PD6), U$1.3 (3A)
BID3: U1.11 (PD7), U$1.4 (4A)
CTS: R4.1, U1.1 (PD3)
GND: 3.3REG.DRAIN (GND), C7.2, C8.2, C9.2, C10.2, C11.1, C12.1, C13.2, C14.2, PWR_LED.C, Q1.2 (S), Q2.2 (S), R8.1, R9.2, RX_LED.C, SCK_LED.C, SV1.6, TX_LED.C, U1.3 (GND_2), U1.5 (GND_3), U1.21 (GND), U$1.5 (4B), U$1.6 (3B), U$1.7 (2B), U$1.8 (1B), U$2.2, XBEE.10 (GND)
MISO: SV1.1, U1.16 (PB4)
MOSI: SV1.4, U1.15 (PB3)
unnamed: R3.2, XBEE.16 (RTS)
unnamed: R13.1, SCK_LED.A
unnamed: R4.2, XBEE.12 (CTS)
unnamed: R1.1, U1.27 (PC4)
unnamed: R10.1, U1.23 (PC0)
unnamed: R6.1, U1.28 (PC5)
unnamed: R14.1, TX_LED.A
unnamed: R15.1, RX_LED.A
unnamed: PWR_LED.A, R16.1
unnamed: Q2.1 (G), R8.2, R10.2, S4.3, S4.4
unnamed: Q1.1 (G), R7.1, R9.1, S2.1, S2.2
RST: Q1.3 (D), R2.1, SV1.5, U1.29 (PC6)
RST_CTRL: R7.2, SV2.4
RTS: R3.1, U1.32 (PD2)
RX: R15.2, RX.P$1, U1.30 (PD0), XBEE.2 (DOUT)
SCK: R13.2, SV1.3, U1.17 (PB5)
TWCK: R6.2, SV2.5
TWD: R1.2, SV2.6
TX: R14.2, TX.P$1, U1.31 (PD1), XBEE.3 (DIN)
XBRST: Q2.3 (D), R5.1, XBEE.5 (RESET)

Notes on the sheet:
RTS/CTS likely not necessary, but can be connected if needed.
